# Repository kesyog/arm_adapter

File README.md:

# arm_adapter

Small addition to Noah's 20-pin to 10-pin ARM JTAG/SWD adapter to include additional connectors in addition to the 10-pin 0.05" connector:
* 6-pin 0.1" through-hole (e.g. Amarok)
* 10-pin 0.1" through-hole (non-standard APC pinout?)
* 10-pin 0.1" through-hole Cortex debug connector (same pin-out as 10-pin 0.05" connector)
* 20-pin 0.05" SMT Debug+Cortex ETM connector

## future improvements

* use shrouded connector for 10-pin 0.05" connector for easier connection
* don't use a right-angle switch?
* fix link to github repo on back silkscreen

## Pictures
### pcb render
TBD
<!---
. . . . . .  
-->

### assembly render
TBD
<!---

-->
### assembled unit
TBD
<!---

-->

## parts

### 10 pin through hole male connector
[digikey](http://www.digikey.com/product-detail/en/te-connectivity-amp-connectors/826656-5/A121773-ND/2276218)  
[digikey](http://www.digikey.com/product-detail/en/20021111-00010T4LF/609-3712-ND/2209072)  
[mouser](http://www.mouser.com/ProductDetail/FCI/20021111-00010T4LF/?qs=sGAEpiMZZMs%252bGHln7q6pmwodwKqstCempwNsK2c%2fC6s%3d)  
[ebay](http://www.ebay.com/itm/12-pcs-Gold-Plated-1-27mm-2x40-80pin-Breakable-Pin-Header-Male-Double-Row-Strip-/370935487630?pt=LH_DefaultDomain_0&hash=item565d7a5c8e)  

[shrouded, digikey](http://www.digikey.com/product-detail/en/3220-10-0100-00/1175-1627-ND/3883661)

### 20 pin through hole female connector
[digikey](http://www.digikey.com/product-detail/en/SFH11-PBPC-D10-ST-BK/S9197-ND/1990090)  
[ebay](http://www.ebay.com/itm/20-Pcs-2x10-Double-Row-20-Pins-PCB-Female-Header-2-54mm-/400316132430?pt=LH_DefaultDomain_0&hash=item5d34b36c4e)  
[digkey right angle](http://www.digikey.com/product-detail/en/SFH11-PBPC-D10-RA-BK/S9205-ND/1990098)  

### 10-pin (2x5) 0.05" SMT male connector
[digikey](http://www.digikey.com/product-detail/en/harwin-inc/M50-3600542/952-1389-ND/2264370)  

### 20-pin (2x10) 0.05" SMT male connector
[digikey](http://www.digikey.com/product-detail/en/amphenol-fci/20021121-00020C4LF/609-3698-1-ND/2209158)  

### 3.3v ldo
Macrofab stocks a 3.3.V 300mA SOT-23-5 LDO  
[mouser- skyworks sot23-5](http://www.mouser.com/ProductDetail/Skyworks-Solutions-Inc/AAT3223IGU-33-T1/?qs=sGAEpiMZZMsGz1a6aV8DcBc9KxeEYlaaHoWA415Wy2k%3d)  
[mouser- TI sot23-5](http://www.mouser.com/ProductDetail/Texas-Instruments/LP5907MFX-33-NOPB/?qs=sGAEpiMZZMsGz1a6aV8DcHd1yzolGFo2Xmtn9ZKMxmA%3d)  
[digikey- TI sot23-5](http://www.digikey.com/product-detail/en/TLV70233DBVR/296-32415-1-ND/3505572)  
[digikey- Micrel sot23-5 300mA](http://www.digikey.com/product-detail/en/MIC5504-3.3YM5%20TR/576-4764-1-ND/4864028)  

### beefier ldo
[mouser- ON](http://www.mouser.com/ProductDetail/ON-Semiconductor/NCP1117LPST33T3G/?qs=sGAEpiMZZMsGz1a6aV8DcG1%252bflTKYVRGzugDxB67PIA%3d)  
[mouser- diodes](http://www.mouser.com/ProductDetail/Diodes-Incorporated/AP1117IE33G-13/?qs=sGAEpiMZZMsGz1a6aV8DcCIlKWhD2GibreMCbJvWdNw%3d)  

### slide switch
[digikey-C&K](http://www.digikey.com/product-detail/en/c-k-components/OS102011MA1QS1/CKN9560-ND/1981431) well-stocked right-angle slide switch  

[mouser- C&K](http://www.mouser.com/ProductDetail/CK-Components/PCM12SMTR/?qs=sGAEpiMZZMsqIr59i2oRcvc9UQrBbcoBkFYgnQFYwWU%3d)  
[digikey- Copal](http://www.digikey.com/product-detail/en/CUS-12TB/563-1102-1-ND/1124231)  
[mouser- ALPS](http://www.mouser.com/ProductDetail/ALPS/SSSS810701/?qs=sGAEpiMZZMtHXLepoqNyVe%252bcQMRoBF1BAzyvwoNmgBo%3d)

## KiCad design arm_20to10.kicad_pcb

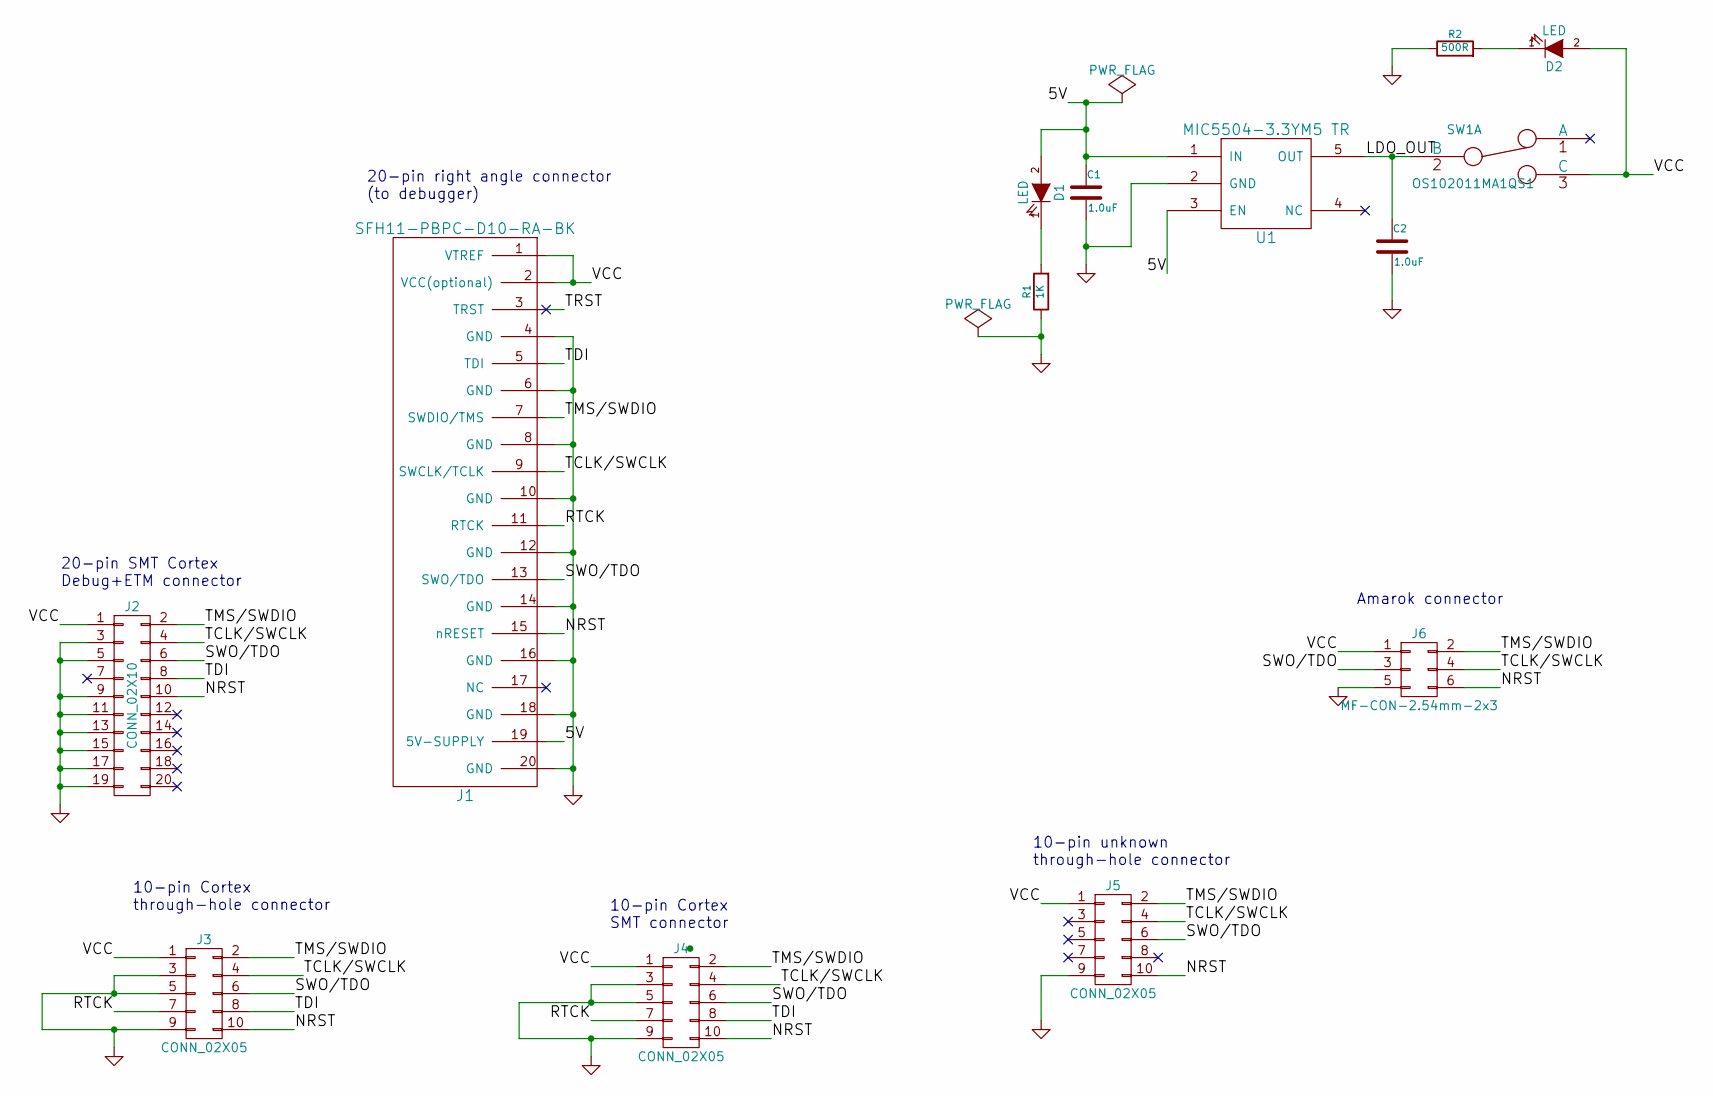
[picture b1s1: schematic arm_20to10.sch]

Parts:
C1, C2: 1.0uF; SMD_0603_C
D1, D2: LED; SMD_0603_LED
J1: SFH11-PBPC-D10-RA-BK; ARM_20_PIN_TH_RIGHTANGLE; MFG PN SFH11-PBPC-D10-RA-BK
J2: CONN_02X10; ARM_20_PIN_SMT
J3, J5: CONN_02X05; Pin_Header_Straight_2x05
J4: CONN_02X05; ARM_10_PIN_SMT
J6: MF-CON-2.54mm-2x3; Pin_Header_Straight_2x03
R1: 1K; SMD_0603_R
R2: 500R; SMD_0603_R
SW1: OS102011MA1QS1; SS-12D07-VG-kes; MFG PN SS-12D07-VG 4 NS GA PA
U1: MIC5504-3.3YM5 TR; sot23-5_noah

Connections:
/5V: C1.1, D1.2 (A), J1.19 (5V-SUPPLY), U1.1 (IN), U1.3 (EN)
/LDO_OUT: C2.1, SW1.2 (B), U1.5 (OUT)
/NRST: J1.15 (nRESET), J2.10, J3.10, J4.10, J5.10, J6.6
/RTCK: J1.11 (RTCK), J3.7, J4.7
/SWO/TDO: J1.13 (SWO/TDO), J2.6, J3.6, J4.6, J5.6, J6.3
/TCLK/SWCLK: J1.9 (SWCLK/TCLK), J2.4, J3.4, J4.4, J5.4, J6.4
/TDI: J1.5 (TDI), J2.8, J3.8, J4.8
/TMS/SWDIO: J1.7 (SWDIO/TMS), J2.2, J3.2, J4.2, J5.2, J6.2
/TRST: J1.3 (TRST)
/VCC: D2.2 (A), J1.1 (VTREF), J1.2 (VCC(optional)), J2.1, J3.1, J4.1, J5.1, J6.1, SW1.3 (C)
GND: C1.2, C2.2, J1.4 (GND), J1.6 (GND), J1.8 (GND), J1.10 (GND), J1.12 (GND), J1.14 (GND), J1.16 (GND), J1.18 (GND), J1.20 (GND), J2.3, J2.5, J2.9, J2.11, J2.13, J2.15, J2.17, J2.19, J3.3, J3.5, J3.9, J4.3, J4.5, J4.9, J5.9, J6.5, R1.1, R2.1, U1.2 (GND)
unnamed: D1.1 (K), R1.2
unnamed: D2.1 (K), R2.2

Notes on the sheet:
Amarok connector
20-pin right angle connector (to debugger)
20-pin SMT Cortex Debug+ETM connector
10-pin Cortex through-hole connector
10-pin Cortex SMT connector
10-pin unknown through-hole connector

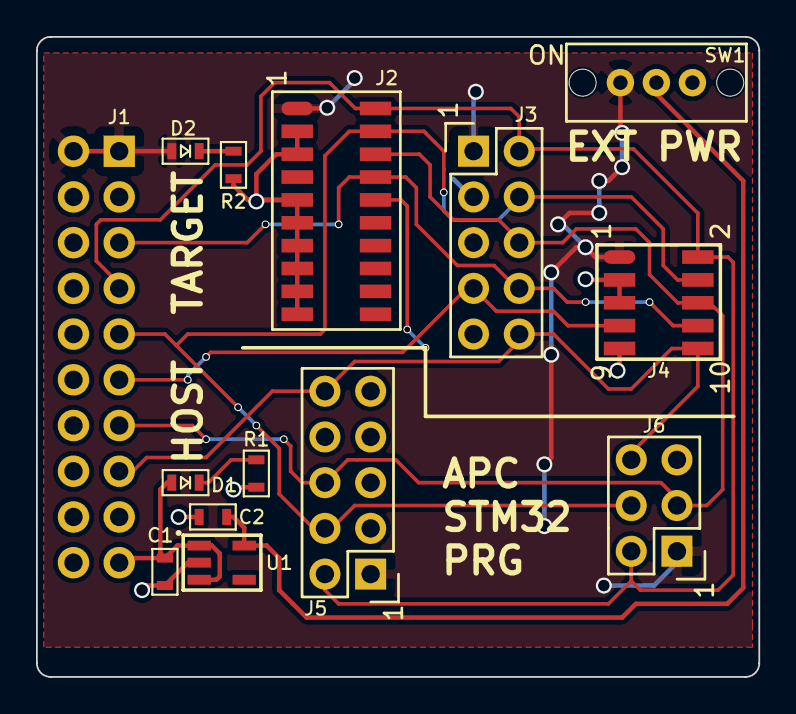
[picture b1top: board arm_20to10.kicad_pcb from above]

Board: 2 copper layers, 40.1 x 35.6 mm, 14 parts (0 on the bottom side), 12 nets.

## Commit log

2016-04-28 Updated Kicad project files for v2.2 build of board. Add my custom library as a submodule. Probably messed up some git commands
2016-04-28 update project description
2016-04-28 add new gerber and BOM
2016-04-28 update project to look in my library for my custom parts rather than Noah's
2016-04-28 updated parts list in project description
